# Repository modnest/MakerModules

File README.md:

# MakerModules-Dev

Entwicklungszweig für MakerModules

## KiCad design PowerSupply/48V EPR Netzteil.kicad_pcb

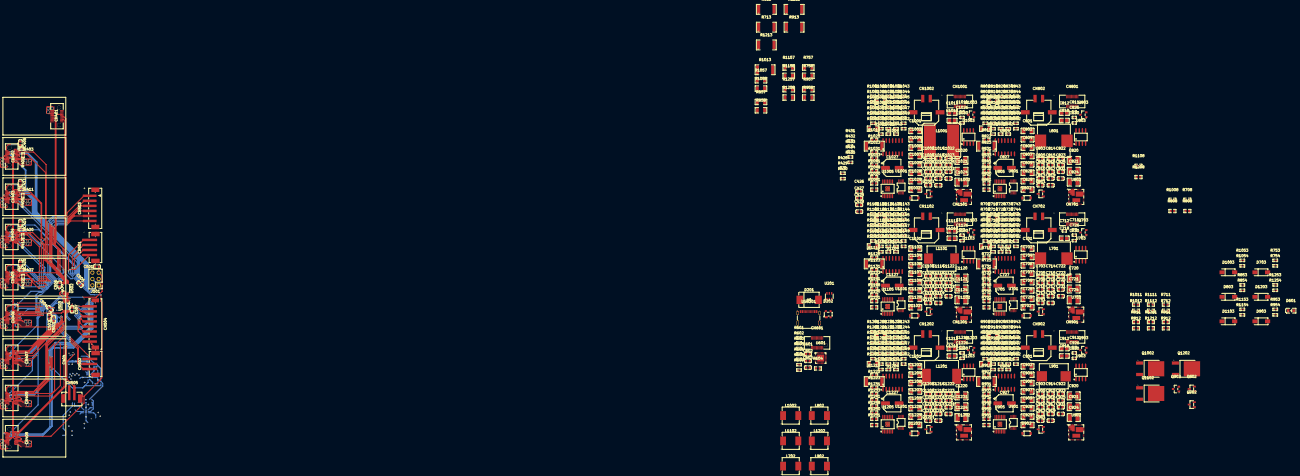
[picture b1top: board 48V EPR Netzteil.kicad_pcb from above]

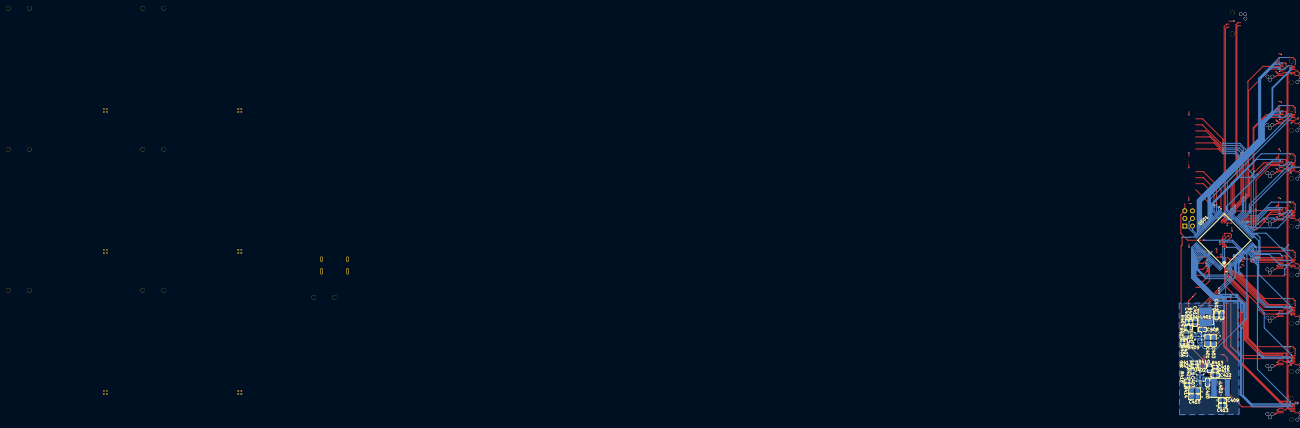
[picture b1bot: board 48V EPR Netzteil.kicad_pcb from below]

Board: 4 copper layers, 699 parts (33 on the bottom side), 487 nets.

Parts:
C401, C407, C718, C818, C918, C1018, C1118, C1218: 100nF X7R 100V; C0805
C402, C404, C409, C413, C705, C710, C722, C805, C810, C822, C905, C910, C922, C1005, C1010, C1022, C1105, C1110, C1122, C1205, C1210, C1222: 10µF; C0603
C403, C410: 2,2µF X7R 63V; C0805
C405, C408, C411, C419, C420, C425, C426, C427, C428, C429, C501, C502, C503, C504, C505, C506, C507, C601, C602, C703, C708, C714, C717, C719, C731, C803, C808, C814, C817, C819, C831, C903, C908, C914, C917, C919, C931, C1003, C1008, C1014, C1017, C1019, C1031, C1103, C1108, C1114, C1117, C1119, C1131, C1203, C1208, C1214, C1217, C1219, C1231: 100nF; C0603
C406: 33pF; C0402
C412, C422, C603, C723, C725, C823, C825, C923, C925, C1023, C1025, C1123, C1125, C1223, C1225: 1µF; C0603
C416: 27pF; C0402
C701, C702, C704, C706, C707, C709, C801, C802, C804, C806, C807, C809, C901, C902, C904, C906, C907, C909, C1001, C1002, C1004, C1006, C1007, C1009, C1101, C1102, C1104, C1106, C1107, C1109, C1201, C1202, C1204, C1206, C1207, C1209: 100µF; C1206
C711: 47pF; C0402
C712: 4,7nf; C0402
C713, C813, C913, C1013, C1113, C1213: 47nF; C0603
C715, C815, C915, C1015, C1115, C1215: 470nF; C0603
C716, C816, C916, C1016, C1116, C1216: 2,2µF; C0603
C720, C721, C724, C820, C821, C824, C920, C921, C924, C1020, C1021, C1024, C1120, C1121, C1124, C1220, C1221, C1224: 10µF 63V; C1210
C726, C826, C926, C1026, C1126, C1226: 10nF; C0402
C727, C827, C927, C1027, C1127, C1227: 22µF; CP_Elec_6.3x7.7
C728, C729, C828, C829, C928, C929, C1028, C1029, C1128, C1129, C1228, C1229: 4,7µF; C1206
C730, C830, C930, C1030, C1130, C1230: 22nF; C0402
C811, C911, C1011, C1111, C1211: 10pF; C0402
C812, C912, C1012, C1112, C1212: 2,2nf; C0805
CN401, CN402, CN403, CN404, CN405, CN406, CN407, CN408, CN409, CN601, CN701, CN801, CN901, CN1001, CN1101, CN1201: LB225-Y20-B0R03; CONN-SMD_LB225-Y20-B0R03
CN501: B4B-PH-SM4-TB; CONN-SMD_B4B-PH-SM4-TB-LF-SN
CN502: B3B-PH-SM4-TB; CONN-SMD_B3B-PH-SM4-TB-LF-SN
CN503: B6B-PH-SM4-TB; CONN-SMD_6P-P2.00_B6B-PH-SM4-TB-LF-SN
CN504: B8B-PH-SM4-TB; CONN-SMD_B8B-PH-SM4-TB-A
CN505: B2B-PH-SM4-TB; CONN-SMD_B2B-PH-SM4-TB-LF-SN
CN702, CN802, CN902, CN1002, CN1102, CN1202: X3025WRS-02D-LPSW; CONN-SMD_2P-H-P3.00-R_X3025WRS-02D-LPSW
D201: SMDJ28A; SMC_L6.9-W5.9-LS7.9-RD
D202: PRTR5V0U2X; SOT-143-4_L2.9-W1.3-P1.92-LS2.4-BL
D601: LED; LED0805-RD
D702, D802, D902, D1002, D1102, D1202: BZT52C12; SOD-123_L2.7-W1.6-LS3.7-RD
D703, D803, D903, D1003, D1103, D1203: SS54; SMA_L4.4-W2.8-LS5.4-R-RD
J501: DEBUG; PinHeader_2x03_P2.54mm_Vertical
L401: 22µH; IND-SMD_L5.0-W5.0
L402: 27µH; IND-SMD_L6.0-W6.0_CR6045K-2R2N
L701: 15µH; IND-SMD_L13.0-W12.8
L702, L802, L902, L1002, L1102, L1202: 8,2µH; IND-SMD_L7.7-W6.6_APS0630M100H
L801: 22µH; IND-SMD_L13.0-W12.8
L901: 8,2µH; IND-SMD_L11.5-W10.0_YSPI1030S
L1001: 12µH; IND-SMD_L13.0-W13.0-SDR1307-XXXXX
L1101: 33µH; IND-SMD_L11.5-W10.0_104CDMCCDS
L1201: 47µH; IND-SMD_L13.5-W12.6_MWSA1206S-470MT
Q701, Q801, Q901, Q1001, Q1101, Q1201: MMBT2222A_C83939; SOT-23-3_L2.9-W1.3-P1.90-LS2.4-BR
Q702, Q802: SI2365EDS; SOT-23-3_L2.9-W1.3-P1.90-LS2.4-BR_Si2365EDS
Q703, Q803, Q902, Q903, Q1003, Q1103, Q1203: AO3401A; SOT-23_L2.9-W1.3-P1.90-LS2.4-BR_AO3401A
Q1002, Q1102, Q1202: AOD409; TO-252-2_L6.6-W6.1-P4.57-LS9.9-TL-CW_AOD409
R401, R403, R405, R406, R411, R412, R414, R416, R417, R420, R422, R427, R428, R429, R430, R431, R432, R433, R434, R435, R601, R602, R701, R702, R706, R710, R716, R724, R727, R734, R737, R749, R752, R801, R802, R806, R810, R816, R824, R827, R834, R837, R849, R852, R901, R902, R906, R910, R916, R924, R927, R934, R937, R949, R952, R1001, R1002, R1006, R1010, R1016, R1024, R1027, R1034, R1037, R1049, R1052, R1101, R1102, R1106, R1110, R1116, R1124, R1127, R1134, R1137, R1149, R1152, R1201, R1202, R1206, R1210, R1216, R1224, R1227, R1234, R1237, R1249, R1252: 10k; R0402
R402: 43k; C0603
R404: 300R; R0603
R407, R424: 1k5; R0402
R408, R415, R703, R715, R728, R730, R743, R744, R803, R815, R828, R830, R843, R844, R903, R915, R928, R930, R943, R944, R1003, R1015, R1028, R1030, R1043, R1044, R1103, R1115, R1128, R1130, R1143, R1144, R1203, R1215, R1228, R1230, R1243, R1244: 100k; R0402
R409, R421: 15k; R0402
R410: 24k; R0603
R413: 820R; R0603
R603, R735, R742, R835, R842, R935, R942, R1035, R1042, R1135, R1142, R1235, R1242: 1k; R0402
R604: 10m; R0603
R605, R606, R704, R705, R804, R805, R904, R905, R1004, R1005, R1104, R1105, R1204, R1205: 100; R0402
R608, R609: 5k1; R0402
R707, R714, R757, R758, R807, R814, R857, R858, R1007, R1014, R1057, R1058, R1107, R1114, R1157, R1158, R1207, R1214, R1257, R1258: 0; R1206
R708: 12k; R0603
R711: 0; R0603
R712, R1008: 13k; R0603
R713, R813, R913, R922, R1013, R1022, R1113, R1213: 10m; R2512
R717, R718, R817, R818, R917, R918, R1017, R1018, R1117, R1118, R1217, R1218: 1k 0,1%; R0402
R719, R819, R919, R1019, R1119, R1219: 39k; R0603
R720, R820, R920, R1020, R1120, R1220: 2k2; R0402
R721, R732, R821, R832: 300k 0,1%; R0402
R722, R822: 39m; R2512
R723, R823, R923, R1023, R1123, R1223: 1R; R0603
R725, R729, R746, R747, R753, R754, R825, R829, R846, R847, R853, R854, R925, R929, R946, R947, R953, R954, R1025, R1029, R1046, R1047, R1053, R1054, R1125, R1129, R1146, R1147, R1153, R1154, R1225, R1229, R1246, R1247, R1253, R1254: 0; R0402
R726, R736, R738, R826, R836, R838, R926, R936, R938, R1026, R1036, R1038, R1126, R1136, R1138, R1226, R1236, R1238: 1M; R0402
R731, R831, R931, R1031, R1131, R1231: 49k9; R0603
R733, R833, R933, R1033, R1133, R1233: 2k4; R0603
R739, R839, R939, R1039, R1139, R1239: ${R_A}; R0402
R740, R840, R940, R1040, R1140, R1240: ${R_B}; R0402
R741, R841, R941, R1041, R1141, R1241: 82k; R0603
R745, R845, R945, R1045, R1145, R1245: ${R_D}; R0402
R748, R911: 1k; R0603
R750, R850, R950, R1050, R1150, R1250: 27k; R0603
R751, R851, R951, R1051, R1151, R1251: 150k; R0603
R808: 8k2; R0603
R811: 1,5k; R0603
R812, R1108: 20k; R0603
R848: 2,2k; R0603
R907, R914, R957, R958: 100m; R1206
R908: 18k; R0603
R912: 33k; R0603
R921, R932, R1021, R1032: 82k 0,1%; R0402
R948, R1011: 3,9k; R0603
R1012: 51k; R0603
R1048: 6,8k; R0603
R1111, R1148: 10k; R0603
R1112: 130k; R0603
R1121, R1132, R1221, R1232: 100k 0,1%; R0402
R1122, R1222: 12m; R2512
R1208: 22k; R0603
R1211: 47k; R0603
R1212: 240k; R0603
R1248: 15k; R0603
U201: USBLC6-2SC6; SOT-23-6_L2.9-W1.6-P0.95-LS2.8-BL
U401, U402: LMR36506RRPER; VQFN-9_L2.0-W2.0-P0.50-TL
U501: STM32G0B1VCT6; LQFP-100_L14.0-W14.0-P0.50-LS16.0-BL
U502, U503: MCP4728T-E/UN; MSOP-10_L3.0-W3.0-P0.50-LS4.9-BL
U601: AP33772SDKZ-13-FA01_C24374260; QFN-24_L4.0-W4.0-P0.50-TL-EP2.8
U701, U801, U901, U1001, U1101, U1201: INA238AIDGSR; VSSOP-10_L3.0-W3.0-P0.50-LS4.9-BL
U702, U802, U902, U1002, U1102, U1202: LM706A0RRXR; VQFN-29_L6.0-W6.0-P0.50_LM70840QRRXR
U703, U803, U903, U1003, U1103, U1203: OPA2197IDR; SOIC-8_L4.9-W3.9-P1.27-LS6.0-BL
U704, U804, U904, U1004, U1104, U1204: LM339DR; SOIC-14_L8.7-W3.9-P1.27-LS6.0-BL
U705, U805, U905, U1005, U1105, U1205: TPS55340PWPR; HTSSOP-14_L5.0-W4.4-P0.65-LS6.4-BL-EP
USB201: HC-TYPE-C-16P-01M; USB-C-SMD_HCTL_HC-TYPE-C-16P-01M

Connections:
/1,8V Supply/A0: CN701.12, U701.2 (A0)
/1,8V Supply/A1: CN701.11, U701.1 (A1)
/1,8V Supply/ALERT: R701.2, R724.1, U701.3 (ALERT)
/1,8V Supply/ALERT_LATCHED: CN701.15, R726.2, R727.1, U704.14 (OUT3)
/1,8V Supply/CC_ACTIVE: CN701.14, R734.1, R736.1, U704.1 (OUT1)
/1,8V Supply/CTRL: C726.2, R702.1, U703.7 (OUT/B)
/1,8V Supply/DETECT: CN701.18, R748.1
/1,8V Supply/EN_BOOST: CN701.20, U705.4 (EN)
/1,8V Supply/EN_BUCK: CN701.13, R743.1, U702.9 (EN/UVLO)
/1,8V Supply/SCL: CN701.10, U701.5 (SCL)
/1,8V Supply/SDA: CN701.9, U701.4 (SDA)
/1,8V Supply/VBUS: C718.1, C720.1, C721.1, C724.1, C728.2, C729.2, C731.2, CN701.1, CN701.3, CN701.5, L702.1, U702.1 (VIN4), U702.3 (VIN6), U705.3 (VIN)
/1,8V Supply/VCC_3V3: C703.2, C705.2, CN701.7, R701.1, U701.6 (VS)
/1,8V Supply/VCC_5V: CN701.8, R747.1
/1,8V Supply/VCC_CTRL: C717.1, C719.2, C722.2, R727.2, R728.1, R734.2, R737.2, R744.1, R746.2, R747.2, U703.8 (+VS), U704.3 (VCC+)
/1,8V Supply/VOUT_BOOST: C723.2, C725.2, C727.1, D703.1 (K), R746.1, R754.1
/1,8V Supply/VOUT_LOW: CN701.16, R737.1, R738.1, U704.2 (OUT2)
/1,8V Supply/V_ISET: CN701.17, R742.1, U704.6 (IN1-)
/1,8V Supply/Vout: D702.1 (K), R706.1, R707.1, R710.1, R711.1, R713.2, R714.1, R718.1, R725.1, R749.1, R757.1, R758.1, U701.8 (VBUS), U701.9 (IN-), U702.12 (VOUT)
/1,8V Supply/Vout_BUCK: C701.1, C702.1, C704.1, C706.1, C707.1, C709.1, R722.1, R753.2
/1,8V Supply/Voutsw: CN702.1, Q702.D, Q703.D, R739.1
/2,5V Supply/A0: CN801.12, U801.2 (A0)
/2,5V Supply/A1: CN801.11, U801.1 (A1)
/2,5V Supply/ALERT: R801.2, R824.1, U801.3 (ALERT)
/2,5V Supply/ALERT_LATCHED: CN801.15, R826.2, R827.1, U804.14 (OUT3)
/2,5V Supply/CC_ACTIVE: CN801.14, R834.1, R836.1, U804.1 (OUT1)
/2,5V Supply/CTRL: C826.2, R802.1, U803.7 (OUT/B)
/2,5V Supply/DETECT: CN801.18, R848.1
/2,5V Supply/EN_BOOST: CN801.20, U805.4 (EN)
/2,5V Supply/EN_BUCK: CN801.13, R843.1, U802.9 (EN/UVLO)
/2,5V Supply/SCL: CN801.10, U801.5 (SCL)
/2,5V Supply/SDA: CN801.9, U801.4 (SDA)
/2,5V Supply/VBUS: C818.1, C820.1, C821.1, C824.1, C828.2, C829.2, C831.2, CN801.1, CN801.3, CN801.5, L802.1, U802.1 (VIN4), U802.3 (VIN6), U805.3 (VIN)
/2,5V Supply/VCC_3V3: C803.2, C805.2, CN801.7, R801.1, U801.6 (VS)
/2,5V Supply/VCC_5V: CN801.8, R847.1
/2,5V Supply/VCC_CTRL: C817.1, C819.2, C822.2, R827.2, R828.1, R834.2, R837.2, R844.1, R846.2, R847.2, U803.8 (+VS), U804.3 (VCC+)
/2,5V Supply/VOUT_BOOST: C823.2, C825.2, C827.1, D803.1 (K), R846.1, R854.1
/2,5V Supply/VOUT_LOW: CN801.16, R837.1, R838.1, U804.2 (OUT2)
/2,5V Supply/V_ISET: CN801.17, R842.1, U804.6 (IN1-)
/2,5V Supply/Vout: D802.1 (K), R806.1, R807.1, R810.1, R811.1, R813.2, R814.1, R818.1, R825.1, R849.1, R857.1, R858.1, U801.8 (VBUS), U801.9 (IN-), U802.12 (VOUT)
/2,5V Supply/Vout_BUCK: C801.1, C802.1, C804.1, C806.1, C807.1, C809.1, R822.1, R853.2
/2,5V Supply/Voutsw: CN802.1, Q802.D, Q803.D, R839.1
/3,3V Supply/A0: CN901.12, U901.2 (A0)
/3,3V Supply/A1: CN901.11, U901.1 (A1)
/3,3V Supply/ALERT: R901.2, R924.1, U901.3 (ALERT)
/3,3V Supply/ALERT_LATCHED: CN901.15, R926.2, R927.1, U904.14 (OUT3)
/3,3V Supply/CC_ACTIVE: CN901.14, R934.1, R936.1, U904.1 (OUT1)
/3,3V Supply/CTRL: C926.2, R902.1, U903.7 (OUT/B)
/3,3V Supply/DETECT: CN901.18, R948.1
/3,3V Supply/EN_BOOST: CN901.20, U905.4 (EN)
/3,3V Supply/EN_BUCK: CN901.13, R943.1, U902.9 (EN/UVLO)
/3,3V Supply/SCL: CN901.10, U901.5 (SCL)
/3,3V Supply/SDA: CN901.9, U901.4 (SDA)
/3,3V Supply/VBUS: C918.1, C920.1, C921.1, C924.1, C928.2, C929.2, C931.2, CN901.1, CN901.3, CN901.5, L902.1, U902.1 (VIN4), U902.3 (VIN6), U905.3 (VIN)
/3,3V Supply/VCC_3V3: C903.2, C905.2, CN901.7, R901.1, U901.6 (VS)
/3,3V Supply/VCC_5V: CN901.8, R947.1
/3,3V Supply/VCC_CTRL: C917.1, C919.2, C922.2, R927.2, R928.1, R934.2, R937.2, R944.1, R946.2, R947.2, U903.8 (+VS), U904.3 (VCC+)
/3,3V Supply/VOUT_BOOST: C923.2, C925.2, C927.1, D903.1 (K), R946.1, R954.1
/3,3V Supply/VOUT_LOW: CN901.16, R937.1, R938.1, U904.2 (OUT2)
/3,3V Supply/V_ISET: CN901.17, R942.1, U904.6 (IN1-)
/3,3V Supply/Vout: D902.1 (K), R906.1, R907.1, R910.1, R911.1, R913.2, R914.1, R918.1, R925.1, R949.1, R957.1, R958.1, U901.8 (VBUS), U901.9 (IN-), U902.12 (VOUT)
/3,3V Supply/Vout_BUCK: C901.1, C902.1, C904.1, C906.1, C907.1, C909.1, R922.1, R953.2
/3,3V Supply/Voutsw: CN902.1, Q902.D, Q903.D, R939.1
/5V Supply/A0: CN1001.12, U1001.2 (A0)
/5V Supply/A1: CN1001.11, U1001.1 (A1)
/5V Supply/ALERT: R1001.2, R1024.1, U1001.3 (ALERT)
/5V Supply/ALERT_LATCHED: CN1001.15, R1026.2, R1027.1, U1004.14 (OUT3)
/5V Supply/CC_ACTIVE: CN1001.14, R1034.1, R1036.1, U1004.1 (OUT1)
/5V Supply/CTRL: C1026.2, R1002.1, U1003.7 (OUT/B)
/5V Supply/DETECT: CN1001.18, R1048.1
/5V Supply/EN_BOOST: CN1001.20, U1005.4 (EN)
/5V Supply/EN_BUCK: CN1001.13, R1043.1, U1002.9 (EN/UVLO)
/5V Supply/SCL: CN1001.10, U1001.5 (SCL)
/5V Supply/SDA: CN1001.9, U1001.4 (SDA)
/5V Supply/VBUS: C1018.1, C1020.1, C1021.1, C1024.1, C1028.2, C1029.2, C1031.2, CN1001.1, CN1001.3, CN1001.5, L1002.1, U1002.1 (VIN4), U1002.3 (VIN6), U1005.3 (VIN)
/5V Supply/VCC_3V3: C1003.2, C1005.2, CN1001.7, R1001.1, U1001.6 (VS)
/5V Supply/VCC_5V: CN1001.8, R1047.1
/5V Supply/VCC_CTRL: C1017.1, C1019.2, C1022.2, R1027.2, R1028.1, R1034.2, R1037.2, R1044.1, R1046.2, R1047.2, U1003.8 (+VS), U1004.3 (VCC+)
/5V Supply/VOUT_BOOST: C1023.2, C1025.2, C1027.1, D1003.1 (K), R1046.1, R1054.1
/5V Supply/VOUT_LOW: CN1001.16, R1037.1, R1038.1, U1004.2 (OUT2)
/5V Supply/V_ISET: CN1001.17, R1042.1, U1004.6 (IN1-)
/5V Supply/Vout: D1002.1 (K), R1006.1, R1007.1, R1010.1, R1011.1, R1013.2, R1014.1, R1018.1, R1025.1, R1049.1, R1057.1, R1058.1, U1001.8 (VBUS), U1001.9 (IN-), U1002.12 (VOUT)
/5V Supply/Vout_BUCK: C1001.1, C1002.1, C1004.1, C1006.1, C1007.1, C1009.1, R1022.1, R1053.2
/5V Supply/Voutsw: CN1002.1, Q1002.D, Q1003.D, R1039.1
/12V Supply/A0: CN1101.12, U1101.2 (A0)
/12V Supply/A1: CN1101.11, U1101.1 (A1)
/12V Supply/ALERT: R1101.2, R1124.1, U1101.3 (ALERT)
/12V Supply/ALERT_LATCHED: CN1101.15, R1126.2, R1127.1, U1104.14 (OUT3)
/12V Supply/CC_ACTIVE: CN1101.14, R1134.1, R1136.1, U1104.1 (OUT1)
/12V Supply/CTRL: C1126.2, R1102.1, U1103.7 (OUT/B)
/12V Supply/DETECT: CN1101.18, R1148.1
/12V Supply/EN_BOOST: CN1101.20, U1105.4 (EN)
/12V Supply/EN_BUCK: CN1101.13, R1143.1, U1102.9 (EN/UVLO)
/12V Supply/SCL: CN1101.10, U1101.5 (SCL)
/12V Supply/SDA: CN1101.9, U1101.4 (SDA)
/12V Supply/VBUS: C1118.1, C1120.1, C1121.1, C1124.1, C1128.2, C1129.2, C1131.2, CN1101.1, CN1101.3, CN1101.5, L1102.1, U1102.1 (VIN4), U1102.3 (VIN6), U1105.3 (VIN)
/12V Supply/VCC_3V3: C1103.2, C1105.2, CN1101.7, R1101.1, U1101.6 (VS)
/12V Supply/VCC_5V: CN1101.8, R1147.1
/12V Supply/VCC_CTRL: C1117.1, C1119.2, C1122.2, R1127.2, R1128.1, R1134.2, R1137.2, R1144.1, R1146.2, R1147.2, U1103.8 (+VS), U1104.3 (VCC+)
/12V Supply/VOUT_BOOST: C1123.2, C1125.2, C1127.1, D1103.1 (K), R1146.1, R1154.1
/12V Supply/VOUT_LOW: CN1101.16, R1137.1, R1138.1, U1104.2 (OUT2)
/12V Supply/V_ISET: CN1101.17, R1142.1, U1104.6 (IN1-)
/12V Supply/Vout: D1102.1 (K), R1106.1, R1107.1, R1110.1, R1111.1, R1113.2, R1114.1, R1118.1, R1125.1, R1149.1, R1157.1, R1158.1, U1101.8 (VBUS), U1101.9 (IN-), U1102.12 (VOUT)
/12V Supply/Vout_BUCK: C1101.1, C1102.1, C1104.1, C1106.1, C1107.1, C1109.1, R1122.1, R1153.2
/12V Supply/Voutsw: CN1102.1, Q1102.D, Q1103.D, R1139.1
/24V Supply/A0: CN1201.12, U1201.2 (A0)
/24V Supply/A1: CN1201.11, U1201.1 (A1)
/24V Supply/ALERT: R1201.2, R1224.1, U1201.3 (ALERT)
/24V Supply/ALERT_LATCHED: CN1201.15, R1226.2, R1227.1, U1204.14 (OUT3)
/24V Supply/CC_ACTIVE: CN1201.14, R1234.1, R1236.1, U1204.1 (OUT1)
/24V Supply/CTRL: C1226.2, R1202.1, U1203.7 (OUT/B)
/24V Supply/DETECT: CN1201.18, R1248.1
/24V Supply/EN_BOOST: CN1201.20, U1205.4 (EN)
/24V Supply/EN_BUCK: CN1201.13, R1243.1, U1202.9 (EN/UVLO)
/24V Supply/SCL: CN1201.10, U1201.5 (SCL)
/24V Supply/SDA: CN1201.9, U1201.4 (SDA)
/24V Supply/VBUS: C1218.1, C1220.1, C1221.1, C1224.1, C1228.2, C1229.2, C1231.2, CN1201.1, CN1201.3, CN1201.5, L1202.1, U1202.1 (VIN4), U1202.3 (VIN6), U1205.3 (VIN)
/24V Supply/VCC_3V3: C1203.2, C1205.2, CN1201.7, R1201.1, U1201.6 (VS)
/24V Supply/VCC_5V: CN1201.8, R1247.1
/24V Supply/VCC_CTRL: C1217.1, C1219.2, C1222.2, R1227.2, R1228.1, R1234.2, R1237.2, R1244.1, R1246.2, R1247.2, U1203.8 (+VS), U1204.3 (VCC+)
/24V Supply/VOUT_BOOST: C1223.2, C1225.2, C1227.1, D1203.1 (K), R1246.1, R1254.1
/24V Supply/VOUT_LOW: CN1201.16, R1237.1, R1238.1, U1204.2 (OUT2)
/24V Supply/V_ISET: CN1201.17, R1242.1, U1204.6 (IN1-)
/24V Supply/Vout: D1202.1 (K), R1206.1, R1207.1, R1210.1, R1211.1, R1213.2, R1214.1, R1218.1, R1225.1, R1249.1, R1257.1, R1258.1, U1201.8 (VBUS), U1201.9 (IN-), U1202.12 (VOUT)
/24V Supply/Vout_BUCK: C1201.1, C1202.1, C1204.1, C1206.1, C1207.1, C1209.1, R1222.1, R1253.2
/24V Supply/Voutsw: CN1202.1, Q1202.D, Q1203.D, R1239.1
/MCU & Peripherals/MCU/DATA.ALERT1: CN402.16, U501.71 (PA12[PA10])
/MCU & Peripherals/MCU/DATA.ALERT2: CN403.16, U501.65 (PD12)
/MCU & Peripherals/MCU/DATA.ALERT3: CN404.16, U501.57 (PC6)
/MCU & Peripherals/MCU/DATA.ALERT4: CN405.16, U501.37 (PB2)
/MCU & Peripherals/MCU/DATA.ALERT5: CN406.16, U501.23 (PC2)
/MCU & Peripherals/MCU/DATA.ALERT6: CN407.16, U501.8 (PC13)
/MCU & Peripherals/MCU/DATA.ALERT7: CN409.16, U501.85 (PD7)
/MCU & Peripherals/MCU/DATA.ALERT8: CN408.16, U501.79 (PD1)
/MCU & Peripherals/MCU/DATA.CC_ACTIVE1: CN402.13, U501.67 (PD14)
/MCU & Peripherals/MCU/DATA.CC_ACTIVE2: CN403.13, U501.59 (PD8)
/MCU & Peripherals/MCU/DATA.CC_ACTIVE3: CN404.13, U501.39 (PF7)
/MCU & Peripherals/MCU/DATA.CC_ACTIVE4: CN405.13, U501.33 (PC4)
/MCU & Peripherals/MCU/DATA.CC_ACTIVE5: CN406.13, U501.10 (PC15-OSC32_OUT)
/MCU & Peripherals/MCU/DATA.CC_ACTIVE6: CN407.13, U501.4 (PE4)
/MCU & Peripherals/MCU/DATA.CC_ACTIVE7: CN409.13, U501.82 (PD4)
/MCU & Peripherals/MCU/DATA.CC_ACTIVE8: CN408.13, U501.76 (PC8)
/MCU & Peripherals/MCU/DATA.DETECT1: CN402.17, R401.1, U501.32 (PA7)
/MCU & Peripherals/MCU/DATA.DETECT2: CN403.17, R405.1, U501.31 (PA6)
/MCU & Peripherals/MCU/DATA.DETECT3: CN404.17, R412.1, U501.30 (PA5)
/MCU & Peripherals/MCU/DATA.DETECT4: CN405.17, R422.1, U501.29 (PA4)
/MCU & Peripherals/MCU/DATA.DETECT5: CN406.17, R428.1, U501.28 (PA3)
/MCU & Peripherals/MCU/DATA.DETECT6: CN407.17, R430.1, U501.27 (PA2)
/MCU & Peripherals/MCU/DATA.DETECT7: CN409.17, R433.1, U501.26 (PA1)
/MCU & Peripherals/MCU/DATA.DETECT8: CN408.17, R432.2, U501.25 (PA0)
/MCU & Peripherals/MCU/DATA.EN1: CN402.14, U501.69 (PA10)
/MCU & Peripherals/MCU/DATA.EN2: CN403.14, U501.61 (PD10)
/MCU & Peripherals/MCU/DATA.EN3: CN404.14, U501.55 (PA8)
/MCU & Peripherals/MCU/DATA.EN4: CN405.14, U501.35 (PB0)
/MCU & Peripherals/MCU/DATA.EN5: CN406.14, U501.18 (PF3)
/MCU & Peripherals/MCU/DATA.EN6: CN407.14, U501.1 (PB9)
/MCU & Peripherals/MCU/DATA.EN7: CN409.14, U501.81 (PD3)
/MCU & Peripherals/MCU/DATA.EN8: CN408.14, U501.75 (PA15)
/MCU & Peripherals/MCU/DATA.EN_BOOST1: CN402.19, U501.72 (PF8)
/MCU & Peripherals/MCU/DATA.EN_BOOST2: CN403.19, U501.66 (PD13)
/MCU & Peripherals/MCU/DATA.EN_BOOST3: CN404.19, U501.58 (PC7)
/MCU & Peripherals/MCU/DATA.EN_BOOST4: CN405.19, U501.38 (PF6)
/MCU & Peripherals/MCU/DATA.EN_BOOST5: CN406.19, U501.24 (PC3)
/MCU & Peripherals/MCU/DATA.EN_BOOST6: CN407.19, U501.9 (PC14-OSC32_IN)
/MCU & Peripherals/MCU/DATA.EN_BOOST7: CN409.19, U501.86 (PF9)
/MCU & Peripherals/MCU/DATA.EN_BOOST8: CN408.19, U501.80 (PD2)
/MCU & Peripherals/MCU/DATA.ISET1: CN402.18, U502.6 (VOUTA)
/MCU & Peripherals/MCU/DATA.ISET2: CN403.18, U502.7 (VOUTB)
/MCU & Peripherals/MCU/DATA.ISET3: CN404.18, U502.8 (VOUTC)
/MCU & Peripherals/MCU/DATA.ISET4: CN405.18, U502.9 (VOUTD)
/MCU & Peripherals/MCU/DATA.ISET5: CN406.18, U503.6 (VOUTA)
/MCU & Peripherals/MCU/DATA.ISET6: CN407.18, U503.7 (VOUTB)
/MCU & Peripherals/MCU/DATA.ISET7: CN409.18, U503.8 (VOUTC)
/MCU & Peripherals/MCU/DATA.ISET8: CN408.18, U503.9 (VOUTD)
/MCU & Peripherals/MCU/DATA.PRESENCE1: C405.1, CN402.20, R403.2, U501.70 (PA11[PA9])
/MCU & Peripherals/MCU/DATA.PRESENCE2: C411.1, CN403.20, R411.2, U501.62 (PD11)
/MCU & Peripherals/MCU/DATA.PRESENCE3: C419.1, CN404.20, R420.2, U501.56 (PA9)
/MCU & Peripherals/MCU/DATA.PRESENCE4: C425.1, CN405.20, R427.2, U501.36 (PB1)
/MCU & Peripherals/MCU/DATA.PRESENCE5: C426.1, CN406.20, R429.2, U501.20 (PF5)
/MCU & Peripherals/MCU/DATA.PRESENCE6: C427.1, CN407.20, R431.2, U501.6 (PE6)
/MCU & Peripherals/MCU/DATA.PRESENCE7: C428.1, CN409.20, R435.2, U501.84 (PD6)
/MCU & Peripherals/MCU/DATA.PRESENCE8: C429.1, CN408.20, R434.2, U501.78 (PD0)
/MCU & Peripherals/MCU/DATA.SCL: CN402.9, CN403.9, CN404.9, CN405.9, CN405.11, CN406.9, CN407.9, CN408.9, CN408.11, CN409.9, U501.21 (PC0)
/MCU & Peripherals/MCU/DATA.SDA: CN402.10, CN403.10, CN404.10, CN404.11, CN405.10, CN406.10, CN407.10, CN408.10, CN409.10, CN409.11, U501.22 (PC1)
/MCU & Peripherals/MCU/DATA.VOUT_LOW1: CN402.15, U501.68 (PD15)
/MCU & Peripherals/MCU/DATA.VOUT_LOW2: CN403.15, U501.60 (PD9)
/MCU & Peripherals/MCU/DATA.VOUT_LOW3: CN404.15, U501.40 (PE7)
/MCU & Peripherals/MCU/DATA.VOUT_LOW4: CN405.15, U501.34 (PC5)
/MCU & Peripherals/MCU/DATA.VOUT_LOW5: CN406.15, U501.19 (PF4)
/MCU & Peripherals/MCU/DATA.VOUT_LOW6: CN407.15, U501.5 (PE5)
/MCU & Peripherals/MCU/DATA.VOUT_LOW7: CN409.15, U501.83 (PD5)
/MCU & Peripherals/MCU/DATA.VOUT_LOW8: CN408.15, U501.77 (PC9)
/MCU & Peripherals/MCU/DISP.BTN1: CN504.1, U501.87 (PF10)
/MCU & Peripherals/MCU/DISP.BTN2: CN504.2, U501.88 (PF11)
/MCU & Peripherals/MCU/DISP.BTN3: CN504.3, U501.89 (PF12)
/MCU & Peripherals/MCU/DISP.BTN4: CN504.4, U501.90 (PF13)
/MCU & Peripherals/MCU/DISP.ENC1: CN504.6, U501.92 (PB4)
/MCU & Peripherals/MCU/DISP.ENC2: CN504.7, U501.93 (PB5)
/MCU & Peripherals/MCU/DISP.ENC_PUSH: CN504.5, U501.91 (PB3)
/MCU & Peripherals/MCU/DISP.LED: CN503.1, CN503.2, U501.41 (PE8), U501.42 (PE9)
/MCU & Peripherals/MCU/DISP.MISO2: CN501.2, U501.53 (PB14)
/MCU & Peripherals/MCU/DISP.MISO3: CN502.2, U501.3 (PC11)
/MCU & Peripherals/MCU/DISP.MOSI2: CN501.3, U501.54 (PB15)
/MCU & Peripherals/MCU/DISP.MOSI3: CN502.3, U501.7 (PC12)
/MCU & Peripherals/MCU/DISP.RESET: CN503.3, U501.43 (PE10)
/MCU & Peripherals/MCU/DISP.SCK1: CN503.4, CN503.5, CN503.6, U501.46 (PE13), U501.47 (PE14), U501.48 (PE15)
/MCU & Peripherals/MCU/DISP.SCK2: CN501.4, U501.52 (PB13)
/MCU & Peripherals/MCU/DISP.SCK3: CN502.1, U501.2 (PC10)
/MCU & Peripherals/MCU/DISP.TIRQ: CN501.1, U501.51 (PB12)
/MCU & Peripherals/MCU/LDAC1: U501.15 (PF0-OSC_IN), U503.4 (~LDAC)
/MCU & Peripherals/MCU/LDAC2: U501.16 (PF1-OSC_OUT), U502.4 (~LDAC)
/MCU & Peripherals/MCU/NRST: C501.2, J501.5, R406.2, U401.2 (PGOOD), U501.17 (PF2-NRST)
/MCU & Peripherals/MCU/PD_SUPPLY.FLIP: CN401.11, U501.44 (PE11)
/MCU & Peripherals/MCU/PD_SUPPLY.INT: CN401.15, U501.45 (PE12)
/MCU & Peripherals/MCU/PD_SUPPLY.SCL2: CN401.14, U501.49 (PB10)
/MCU & Peripherals/MCU/PD_SUPPLY.SDA2: CN401.10, U501.50 (PB11)
/MCU & Peripherals/MCU/SCL_ISET: U501.98 (PB6), U502.2 (SCL), U503.2 (SCL)
/MCU & Peripherals/MCU/SDA_ISET: U501.99 (PB7), U502.3 (SDA), U503.3 (SDA)
/MCU & Peripherals/MCU/SWDCLK: J501.4, U501.74 (PA14-BOOT0)
/MCU & Peripherals/MCU/SWDIO: J501.2, U501.73 (PA13)
/MCU & Peripherals/MCU/Vdd: C402.1, C404.1, C406.2, C502.1, C503.2, C504.2, C505.2, C506.1, C507.2, CN401.7, CN402.8, CN403.8, CN403.11, CN404.8, CN405.8, CN406.8, CN406.12, CN407.8, CN407.11, CN407.12, CN408.8, CN408.12, CN409.8, CN409.12, CN505.1, J501.1, L401.1, R401.2, R403.1, R405.2, R406.1, R408.2, R411.1, R412.2, R417.1, R420.1, R422.2, R427.1, R428.2, R429.1, R430.2, R431.1, R432.1, R433.2, R434.1, R435.1, U501.11 (VBAT), U501.12 (VREF+), U501.13 (VDD/VDDA), U501.64 (VDDIO2), U502.1 (VDD), U502.10 (VSS), U503.1 (VDD), U503.10 (VSS)
/MCU & Peripherals/Mainboard/FB3V3: C406.1, R404.2, R408.1, U401.8 (FB)
/MCU & Peripherals/Mainboard/FB5VBIAS: C416.1, R413.2, R415.1, U402.8 (FB)
/MCU & Peripherals/Mainboard/PGOOD_5V: R417.2, U402.2 (PGOOD)
/MCU & Peripherals/Mainboard/POWER.5V: C409.1, C413.1, C416.2, CN402.7, CN403.7, CN404.7, CN405.7, CN406.7, CN407.7, CN408.7, CN409.7, L402.1, R415.2
/MCU & Peripherals/Mainboard/POWER.VBUS: C401.2, C403.2, C407.2, C410.2, CN401.2, CN401.4, CN401.6, CN402.2, CN402.4, CN402.6, CN403.2, CN403.4, CN403.6, CN404.2, CN404.4, CN404.6, CN405.2, CN405.4, CN405.6, CN406.2, CN406.4, CN406.6, CN407.2, CN407.4, CN407.6, CN408.2, CN408.4, CN408.6, CN409.2, CN409.4, CN409.6, U401.3 (EN/UVLO), U401.4 (VIN), U402.4 (VIN)
/Power Supply/3V3: CN601.8, R601.2, R602.2
/Power Supply/CC1: D202.2 (I/O1), R608.1, U601.17 (CC1), USB201.A5 (CC1)
/Power Supply/CC2: D202.3 (I/O2), R609.1, U601.16 (CC2), USB201.B5 (CC2)
/Power Supply/DN: U201.3 (I/O2), U201.6 (I/O1), U601.18 (DN), USB201.A7 (DN1), USB201.B7 (DN2)
/Power Supply/DP: U201.1 (I/O1), U201.4 (I/O2), U601.19 (DP), USB201.A6 (DP1), USB201.B6 (DP2)
/Power Supply/FLIP: CN601.12, U601.6 (FLIP)
/Power Supply/INT: CN601.16, U601.9 (INT)
/Power Supply/SCL: CN601.13, R601.1, U601.5 (SCL)
/Power Supply/SDA: CN601.9, R602.1, U601.4 (SDA)
/Power Supply/VBUS_RAW: R604.1, U601.1 (ISENP)
/Power Supply/VOUT_RAW: CN601.1, CN601.3, CN601.5
/USB-C Connector & Protection/VBUS: D201.1 (A1), USB201.A4 (VBUS), USB201.A9 (VBUS), USB201.B4 (VBUS), USB201.B9 (VBUS)
GND: C401.1, C402.2, C403.1, C404.2, C405.2, C407.1, C409.2, C410.1, C411.2, C412.1, C413.2, C419.2, C422.1, C425.2, C426.2, C427.2, C428.2, C429.2, C501.1, C502.2, C503.1, C504.1, C505.1, C506.2, C507.1, C601.2, C602.2, C603.2, C701.2, C702.2, C703.1, C704.2, C705.1, C706.2, C707.2, C708.1, C709.2, C710.1, C711.2, C712.2, C714.2, C715.2, C716.2, C717.2, C718.2, C719.1, C720.2, C721.2, C722.1, C723.1, C724.2, C725.1, C727.2, C728.1, C729.1, C730.2, C731.1, C801.2, C802.2, C803.1, C804.2, C805.1, C806.2, C807.2, C808.1, C809.2, C810.1, C811.2, C812.2, C814.2, C815.2, C816.2, C817.2, C818.2, C819.1, C820.2, C821.2, C822.1, C823.1, C824.2, C825.1, C827.2, C828.1, C829.1, C830.2, C831.1, C901.2, C902.2, C903.1, C904.2, C905.1, C906.2, C907.2, C908.1, C909.2, C910.1, C911.2, C912.2, C914.2, C915.2, C916.2, C917.2, C918.2, C919.1, C920.2, C921.2, C922.1, C923.1, C924.2, C925.1, C927.2, C928.1, C929.1, C930.2, C931.1, C1001.2, C1002.2, C1003.1, C1004.2, C1005.1, C1006.2, C1007.2, C1008.1, C1009.2, C1010.1, C1011.2, C1012.2, C1014.2, C1015.2, C1016.2, C1017.2, C1018.2, C1019.1, C1020.2, C1021.2, C1022.1, C1023.1, C1024.2, C1025.1, C1027.2, C1028.1, C1029.1, C1030.2, C1031.1, C1101.2, C1102.2, C1103.1, C1104.2, C1105.1, C1106.2, C1107.2, C1108.1, C1109.2, C1110.1, C1111.2, C1112.2, C1114.2, C1115.2, C1116.2, C1117.2, C1118.2, C1119.1, C1120.2, C1121.2, C1122.1, C1123.1, C1124.2, C1125.1, C1127.2, C1128.1, C1129.1, C1130.2, C1131.1, C1201.2, C1202.2, C1203.1, C1204.2, C1205.1, C1206.2, C1207.2, C1208.1, C1209.2, C1210.1, C1211.2, C1212.2, C1214.2, C1215.2, C1216.2, C1217.2, C1218.2, C1219.1, C1220.2, C1221.2, C1222.1, C1223.1, C1224.2, C1225.1, C1227.2, C1228.1, C1229.1, C1230.2, C1231.1, CN401.1, CN401.3, CN401.5, CN401.8, CN401.9, CN401.12, CN401.13, CN401.16, CN401.17, CN401.18, CN401.19, CN401.20, CN402.1, CN402.3, CN402.5, CN402.11, CN402.12, CN403.1, CN403.3, CN403.5, CN403.12, CN404.1, CN404.3, CN404.5, CN404.12, CN405.1, CN405.3, CN405.5, CN405.12, CN406.1, CN406.3, CN406.5, CN406.11, CN407.1, CN407.3, CN407.5, CN408.1, CN408.3, CN408.5, CN409.1, CN409.3, CN409.5, CN501.5, CN501.6, CN502.4, CN502.5, CN503.7, CN503.8, CN504.8, CN504.9, CN504.10, CN505.2, CN505.3, CN505.4, CN601.2, CN601.4, CN601.6, CN601.7, CN601.10, CN601.11, CN601.14, CN601.15, CN601.17, CN601.18, CN601.19, CN601.20, CN701.2, CN701.4, CN701.6, CN701.19, CN702.2, CN801.2, CN801.4, CN801.6, CN801.19, CN802.2, CN901.2, CN901.4, CN901.6, CN901.19, CN902.2, CN1001.2, CN1001.4, CN1001.6, CN1001.19, CN1002.2, CN1101.2, CN1101.4, CN1101.6, CN1101.19, CN1102.2, CN1201.2, CN1201.4, CN1201.6, CN1201.19, CN1202.2, D201.2 (A2), D202.1 (GND), D601.1 (K), J501.3, J501.6, Q701.2 (E), Q801.2 (E), Q901.2 (E), Q1001.2 (E), Q1101.2 (E), Q1201.2 (E), R402.1, R407.2, R410.1, R416.1, R424.1, R608.2, R609.2, R703.2, R716.2, R720.2, R721.2, R729.1, R730.2, R733.1, R740.2, R743.2, R745.2, R748.2, R752.2, R803.2, R816.2, R820.2, R821.2, R829.1, R830.2, R833.1, R840.2, R843.2, R845.2, R848.2, R852.2, R903.2, R916.2, R920.2, R921.2, R929.1, R930.2, R933.1, R940.2, R943.2, R945.2, R948.2, R952.2, R1003.2, R1016.2, R1020.2, R1021.2, R1029.1, R1030.2, R1033.1, R1040.2, R1043.2, R1045.2, R1048.2, R1052.2, R1103.2, R1116.2, R1120.2, R1121.2, R1129.1, R1130.2, R1133.1, R1140.2, R1143.2, R1145.2, R1148.2, R1152.2, R1203.2, R1216.2, R1220.2, R1221.2, R1229.1, R1230.2, R1233.1, R1240.2, R1243.2, R1245.2, R1248.2, R1252.2, U201.2 (GND), U401.9 (GND), U402.9 (GND), U501.14 (VSS/VSSA), U501.63 (VSS), U601.3 (GND), U601.25 (EP), U701.7 (GND), U702.8 (PFM/SYNCIN), U702.17 (AGND), U702.23 (PGND1), U702.24 (PGND2), U702.25 (PGND3), U702.26 (PGND4), U702.30 (PGND), U703.4 (-VS), U704.10 (IN4-), U704.11 (IN4+), U704.12 (VCC-), U705.7 (AGND), U705.11 (NC), U705.12 (PGND), U705.13 (PGND), U705.14 (PGND), U705.15 (EP), U801.7 (GND), U802.8 (PFM/SYNCIN), U802.17 (AGND), U802.23 (PGND1), U802.24 (PGND2), U802.25 (PGND3), U802.26 (PGND4), U802.30 (PGND), U803.4 (-VS), U804.10 (IN4-), U804.11 (IN4+), U804.12 (VCC-), U805.7 (AGND), U805.11 (NC), U805.12 (PGND), U805.13 (PGND), U805.14 (PGND), U805.15 (EP), U901.7 (GND), U902.8 (PFM/SYNCIN), U902.17 (AGND), U902.23 (PGND1), U902.24 (PGND2), U902.25 (PGND3), U902.26 (PGND4), U902.30 (PGND), U903.4 (-VS), U904.10 (IN4-), U904.11 (IN4+), U904.12 (VCC-), U905.7 (AGND), U905.11 (NC), U905.12 (PGND), U905.13 (PGND), U905.14 (PGND), U905.15 (EP), U1001.7 (GND), U1002.8 (PFM/SYNCIN), U1002.17 (AGND), U1002.23 (PGND1), U1002.24 (PGND2), U1002.25 (PGND3), U1002.26 (PGND4), U1002.30 (PGND), U1003.4 (-VS), U1004.10 (IN4-), U1004.11 (IN4+), U1004.12 (VCC-), U1005.7 (AGND), U1005.11 (NC), U1005.12 (PGND), U1005.13 (PGND), U1005.14 (PGND), U1005.15 (EP), U1101.7 (GND), U1102.8 (PFM/SYNCIN), U1102.17 (AGND), U1102.23 (PGND1), U1102.24 (PGND2), U1102.25 (PGND3), U1102.26 (PGND4), U1102.30 (PGND), U1103.4 (-VS), U1104.10 (IN4-), U1104.11 (IN4+), U1104.12 (VCC-), U1105.7 (AGND), U1105.11 (NC), U1105.12 (PGND), U1105.13 (PGND), U1105.14 (PGND), U1105.15 (EP), U1201.7 (GND), U1202.8 (PFM/SYNCIN), U1202.17 (AGND), U1202.23 (PGND1), U1202.24 (PGND2), U1202.25 (PGND3), U1202.26 (PGND4), U1202.30 (PGND), U1203.4 (-VS), U1204.10 (IN4-), U1204.11 (IN4+), U1204.12 (VCC-), U1205.7 (AGND), U1205.11 (NC), U1205.12 (PGND), U1205.13 (PGND), U1205.14 (PGND), U1205.15 (EP), USB201.25 (EH), USB201.26 (EH), USB201.27 (EH), USB201.28 (EH), USB201.A1 (GND), USB201.A12 (GND), USB201.B1 (GND), USB201.B12 (GND)
unnamed: C713.2, R723.1
unnamed: C726.1, R741.2
unnamed: C813.2, R823.1
unnamed: C826.1, R841.2
unnamed: C913.2, R923.1
unnamed: C926.1, R941.2
unnamed: C1013.2, R1023.1
unnamed: C1026.1, R1041.2
unnamed: C1113.2, R1123.1
unnamed: C1126.1, R1141.2
unnamed: C1213.2, R1223.1
unnamed: C1226.1, R1241.2
unnamed: D601.2 (A), R603.1
unnamed: D702.2 (A), Q702.G, R704.2, R706.2
unnamed: D703.2 (A), L702.2, U705.1 (SW), U705.2 (SW)
unnamed: D802.2 (A), Q802.G, R804.2, R806.2
unnamed: D803.2 (A), L802.2, U805.1 (SW), U805.2 (SW)
unnamed: D902.2 (A), Q902.G, R904.2, R906.2
unnamed: D903.2 (A), L902.2, U905.1 (SW), U905.2 (SW)
unnamed: D1002.2 (A), Q1002.G, R1004.2, R1006.2
unnamed: D1003.2 (A), L1002.2, U1005.1 (SW), U1005.2 (SW)
unnamed: D1102.2 (A), Q1102.G, R1104.2, R1106.2
unnamed: D1103.2 (A), L1102.2, U1105.1 (SW), U1105.2 (SW)
unnamed: D1202.2 (A), Q1202.G, R1204.2, R1206.2
unnamed: D1203.2 (A), L1202.2, U1205.1 (SW), U1205.2 (SW)
unnamed: R604.2, U601.24 (VCC)
unnamed: Q701.1 (B), R702.2, R703.1
unnamed: Q701.3 (C), R704.1, R705.1
unnamed: Q702.S, R707.2
unnamed: Q703.G, R705.2, R710.2
unnamed: Q703.S, R714.2, R757.2, R758.2
unnamed: Q801.1 (B), R802.2, R803.1
unnamed: Q801.3 (C), R804.1, R805.1
unnamed: Q802.S, R807.2
unnamed: Q803.G, R805.2, R810.2
unnamed: Q803.S, R814.2, R857.2, R858.2
unnamed: Q901.1 (B), R902.2, R903.1
unnamed: Q901.3 (C), R904.1, R905.1
unnamed: Q902.S, R907.2
unnamed: Q903.G, R905.2, R910.2
unnamed: Q903.S, R914.2, R957.2, R958.2
unnamed: Q1001.1 (B), R1002.2, R1003.1
unnamed: Q1001.3 (C), R1004.1, R1005.1
unnamed: Q1002.S, R1007.2
unnamed: Q1003.G, R1005.2, R1010.2
unnamed: Q1003.S, R1014.2, R1057.2, R1058.2
unnamed: Q1101.1 (B), R1102.2, R1103.1
unnamed: Q1101.3 (C), R1104.1, R1105.1
unnamed: Q1102.S, R1107.2
unnamed: Q1103.G, R1105.2, R1110.2
unnamed: Q1103.S, R1114.2, R1157.2, R1158.2
unnamed: Q1201.1 (B), R1202.2, R1203.1
unnamed: Q1201.3 (C), R1204.1, R1205.1
unnamed: Q1202.S, R1207.2
unnamed: Q1203.G, R1205.2, R1210.2
unnamed: Q1203.S, R1214.2, R1257.2, R1258.2
unnamed: R402.2, R404.1
unnamed: R407.1, R409.1
unnamed: R410.2, R413.1
unnamed: R421.2, R424.2
unnamed: R711.2, R712.1
unnamed: R719.2, R720.1
unnamed: R731.2, R733.2
unnamed: R749.2, R750.1
unnamed: R750.2, R751.1
unnamed: R811.2, R812.1
unnamed: R819.2, R820.1
unnamed: R831.2, R833.2
unnamed: R849.2, R850.1
unnamed: R850.2, R851.1
unnamed: R911.2, R912.1
unnamed: R919.2, R920.1
unnamed: R931.2, R933.2
unnamed: R949.2, R950.1
unnamed: R950.2, R951.1
unnamed: R1011.2, R1012.1
unnamed: R1019.2, R1020.1
unnamed: R1031.2, R1033.2
unnamed: R1049.2, R1050.1
unnamed: R1050.2, R1051.1
unnamed: R1111.2, R1112.1
unnamed: R1119.2, R1120.1
unnamed: R1131.2, R1133.2
unnamed: R1149.2, R1150.1
unnamed: R1150.2, R1151.1
unnamed: R1211.2, R1212.1
unnamed: R1219.2, R1220.1
unnamed: R1231.2, R1233.2
unnamed: R1249.2, R1250.1
unnamed: R1250.2, R1251.1
unnamed: C408.2, U401.6 (BOOT)
unnamed: R409.2, U401.1 (RT)
unnamed: C408.1, L401.2, U401.5 (SW)
unnamed: C412.2, U401.7 (VCC)
unnamed: C420.2, U402.6 (BOOT)
unnamed: R414.2, R416.2, U402.3 (EN/UVLO)
unnamed: R421.1, U402.1 (RT)
unnamed: C420.1, L402.2, U402.5 (SW)
unnamed: C422.2, U402.7 (VCC)
unnamed: C602.1, U601.15 (IFB)
unnamed: R603.2, U601.8 (LED)
unnamed: R605.2, R606.2, U601.23 (PWR_EN)
unnamed: C603.1, U601.20 (V5V)
unnamed: C601.1, U601.12 (V18)
unnamed: C708.2, C710.2, R713.1, R717.1, R753.1, R754.2, U701.10 (IN+)
unnamed: R725.2, R729.2, U702.6 (BIAS)
unnamed: C713.1, U702.4 (CBOOT)
unnamed: R719.1, U702.13 (CONFIG)
unnamed: C711.1, R708.1, U702.15 (EXTCOMP)
unnamed: R712.2, R716.1, U702.16 (FB)
unnamed: L701.1, R722.2, U702.11 (ISNS+)
unnamed: R715.2, U702.7 (PG/SYNCOUT)
unnamed: R731.1, U702.14 (RT)
unnamed: L701.2, U702.20 (SW1)
unnamed: R723.2, U702.5 (SW4)
unnamed: C716.1, U702.19 (VCC)
unnamed: C715.1, R715.1, U702.18 (VDDA)
unnamed: R718.2, R721.1, U703.3 (+IN/A)
unnamed: R742.2, U703.5 (+IN/B)
unnamed: R717.2, R732.1, U703.2 (-IN/A)
unnamed: R735.2, R741.1, U703.6 (-IN/B)
unnamed: R732.2, R735.1, R736.2, U703.1 (OUT/A), U704.7 (IN1+)
unnamed: R738.2, R739.2, R740.1, U704.5 (IN2+)
unnamed: R744.2, R745.1, U704.4 (IN2-)
unnamed: C714.1, R724.2, R726.1, U704.9 (IN3+)
unnamed: R728.2, R730.1, U704.8 (IN3-)
unnamed: R751.2, R752.1, U705.9 (FB)
unnamed: C730.1, U705.5 (SS)
unnamed: C808.2, C810.2, R813.1, R817.1, R853.1, R854.2, U801.10 (IN+)
unnamed: R825.2, R829.2, U802.6 (BIAS)
unnamed: C813.1, U802.4 (CBOOT)
unnamed: R819.1, U802.13 (CONFIG)
unnamed: C811.1, R808.1, U802.15 (EXTCOMP)
unnamed: R812.2, R816.1, U802.16 (FB)
unnamed: L801.1, R822.2, U802.11 (ISNS+)
unnamed: R815.2, U802.7 (PG/SYNCOUT)
unnamed: R831.1, U802.14 (RT)
unnamed: L801.2, U802.20 (SW1)
unnamed: R823.2, U802.5 (SW4)
unnamed: C816.1, U802.19 (VCC)
unnamed: C815.1, R815.1, U802.18 (VDDA)
unnamed: R818.2, R821.1, U803.3 (+IN/A)
unnamed: R842.2, U803.5 (+IN/B)
unnamed: R817.2, R832.1, U803.2 (-IN/A)
unnamed: R835.2, R841.1, U803.6 (-IN/B)
unnamed: R832.2, R835.1, R836.2, U803.1 (OUT/A), U804.7 (IN1+)
unnamed: R838.2, R839.2, R840.1, U804.5 (IN2+)
unnamed: R844.2, R845.1, U804.4 (IN2-)
unnamed: C814.1, R824.2, R826.1, U804.9 (IN3+)
unnamed: R828.2, R830.1, U804.8 (IN3-)
unnamed: R851.2, R852.1, U805.9 (FB)
unnamed: C830.1, U805.5 (SS)
unnamed: C908.2, C910.2, R913.1, R917.1, R953.1, R954.2, U901.10 (IN+)
unnamed: R925.2, R929.2, U902.6 (BIAS)
unnamed: C913.1, U902.4 (CBOOT)
unnamed: R919.1, U902.13 (CONFIG)
unnamed: C911.1, R908.1, U902.15 (EXTCOMP)
unnamed: R912.2, R916.1, U902.16 (FB)
unnamed: L901.1, R922.2, U902.11 (ISNS+)
unnamed: R915.2, U902.7 (PG/SYNCOUT)
unnamed: R931.1, U902.14 (RT)
unnamed: L901.2, U902.20 (SW1)
unnamed: R923.2, U902.5 (SW4)
unnamed: C916.1, U902.19 (VCC)
unnamed: C915.1, R915.1, U902.18 (VDDA)
unnamed: R918.2, R921.1, U903.3 (+IN/A)
unnamed: R942.2, U903.5 (+IN/B)
unnamed: R917.2, R932.1, U903.2 (-IN/A)
unnamed: R935.2, R941.1, U903.6 (-IN/B)
unnamed: R932.2, R935.1, R936.2, U903.1 (OUT/A), U904.7 (IN1+)
unnamed: R938.2, R939.2, R940.1, U904.5 (IN2+)
unnamed: R944.2, R945.1, U904.4 (IN2-)
unnamed: C914.1, R924.2, R926.1, U904.9 (IN3+)
unnamed: R928.2, R930.1, U904.8 (IN3-)
unnamed: R951.2, R952.1, U905.9 (FB)
unnamed: C930.1, U905.5 (SS)
unnamed: C1008.2, C1010.2, R1013.1, R1017.1, R1053.1, R1054.2, U1001.10 (IN+)
unnamed: R1025.2, R1029.2, U1002.6 (BIAS)
unnamed: C1013.1, U1002.4 (CBOOT)
unnamed: R1019.1, U1002.13 (CONFIG)
unnamed: C1011.1, R1008.1, U1002.15 (EXTCOMP)
unnamed: R1012.2, R1016.1, U1002.16 (FB)
unnamed: L1001.1, R1022.2, U1002.11 (ISNS+)
unnamed: R1015.2, U1002.7 (PG/SYNCOUT)
unnamed: R1031.1, U1002.14 (RT)
unnamed: L1001.2, U1002.20 (SW1)
unnamed: R1023.2, U1002.5 (SW4)
unnamed: C1016.1, U1002.19 (VCC)
unnamed: C1015.1, R1015.1, U1002.18 (VDDA)
unnamed: R1018.2, R1021.1, U1003.3 (+IN/A)
unnamed: R1042.2, U1003.5 (+IN/B)
unnamed: R1017.2, R1032.1, U1003.2 (-IN/A)
unnamed: R1035.2, R1041.1, U1003.6 (-IN/B)
unnamed: R1032.2, R1035.1, R1036.2, U1003.1 (OUT/A), U1004.7 (IN1+)
unnamed: R1038.2, R1039.2, R1040.1, U1004.5 (IN2+)
unnamed: R1044.2, R1045.1, U1004.4 (IN2-)
unnamed: C1014.1, R1024.2, R1026.1, U1004.9 (IN3+)
unnamed: R1028.2, R1030.1, U1004.8 (IN3-)
unnamed: R1051.2, R1052.1, U1005.9 (FB)
unnamed: C1030.1, U1005.5 (SS)
unnamed: C1108.2, C1110.2, R1113.1, R1117.1, R1153.1, R1154.2, U1101.10 (IN+)
unnamed: R1125.2, R1129.2, U1102.6 (BIAS)
unnamed: C1113.1, U1102.4 (CBOOT)
unnamed: R1119.1, U1102.13 (CONFIG)
unnamed: C1111.1, R1108.1, U1102.15 (EXTCOMP)
unnamed: R1112.2, R1116.1, U1102.16 (FB)
unnamed: L1101.1, R1122.2, U1102.11 (ISNS+)
unnamed: R1115.2, U1102.7 (PG/SYNCOUT)
unnamed: R1131.1, U1102.14 (RT)
unnamed: L1101.2, U1102.20 (SW1)
unnamed: R1123.2, U1102.5 (SW4)
unnamed: C1116.1, U1102.19 (VCC)
unnamed: C1115.1, R1115.1, U1102.18 (VDDA)
unnamed: R1118.2, R1121.1, U1103.3 (+IN/A)
unnamed: R1142.2, U1103.5 (+IN/B)
unnamed: R1117.2, R1132.1, U1103.2 (-IN/A)
unnamed: R1135.2, R1141.1, U1103.6 (-IN/B)
unnamed: R1132.2, R1135.1, R1136.2, U1103.1 (OUT/A), U1104.7 (IN1+)
unnamed: R1138.2, R1139.2, R1140.1, U1104.5 (IN2+)
unnamed: R1144.2, R1145.1, U1104.4 (IN2-)
unnamed: C1114.1, R1124.2, R1126.1, U1104.9 (IN3+)
unnamed: R1128.2, R1130.1, U1104.8 (IN3-)
unnamed: R1151.2, R1152.1, U1105.9 (FB)
unnamed: C1130.1, U1105.5 (SS)
unnamed: C1208.2, C1210.2, R1213.1, R1217.1, R1253.1, R1254.2, U1201.10 (IN+)
unnamed: R1225.2, R1229.2, U1202.6 (BIAS)
unnamed: C1213.1, U1202.4 (CBOOT)
unnamed: R1219.1, U1202.13 (CONFIG)
unnamed: C1211.1, R1208.1, U1202.15 (EXTCOMP)
unnamed: R1212.2, R1216.1, U1202.16 (FB)
unnamed: L1201.1, R1222.2, U1202.11 (ISNS+)
unnamed: R1215.2, U1202.7 (PG/SYNCOUT)
unnamed: R1231.1, U1202.14 (RT)
unnamed: L1201.2, U1202.20 (SW1)
unnamed: R1223.2, U1202.5 (SW4)
unnamed: C1216.1, U1202.19 (VCC)
unnamed: C1215.1, R1215.1, U1202.18 (VDDA)
unnamed: R1218.2, R1221.1, U1203.3 (+IN/A)
unnamed: R1242.2, U1203.5 (+IN/B)
unnamed: R1217.2, R1232.1, U1203.2 (-IN/A)
unnamed: R1235.2, R1241.1, U1203.6 (-IN/B)
unnamed: R1232.2, R1235.1, R1236.2, U1203.1 (OUT/A), U1204.7 (IN1+)
unnamed: R1238.2, R1239.2, R1240.1, U1204.5 (IN2+)
unnamed: R1244.2, R1245.1, U1204.4 (IN2-)
unnamed: C1214.1, R1224.2, R1226.1, U1204.9 (IN3+)
unnamed: R1228.2, R1230.1, U1204.8 (IN3-)
unnamed: R1251.2, R1252.1, U1205.9 (FB)
unnamed: C1230.1, U1205.5 (SS)

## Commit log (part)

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2026-04-30 Add project directory structure
2026-04-30 Add PowerSupply KiCad project
2026-04-30 Symbole auf Standard geändert
2026-05-06 Mainboard angepasst
2026-05-06 Schaltplanstand als PDF
